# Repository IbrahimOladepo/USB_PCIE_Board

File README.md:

# USB PCIe Expansion Card

A PCI Express x1 to USB 3.0 expansion card, designed in KiCad. Plugs into a PCIe x1
slot and breaks it out to four USB 3.0 Type-A ports.

## Contents

- [Overview](#overview)
- [Board](#board)
- [Design approach](#design-approach)
- [First assembled board (v0.1)](#first-assembled-board-v01)
  - [The R25 bring-up bug and the through-hole fix](#the-r25-bring-up-bug-and-the-through-hole-fix)
  - [Running in a PC](#running-in-a-pc)
  - [Known issues](#known-issues-to-fix-in-the-next-revision)
- [Component sorting tray](#component-sorting-tray)
- [OS / driver setup](#os--driver-setup)
  - [Windows](#windows)
  - [Linux](#linux)
- [Repository layout](#repository-layout)
- [Status](#status)

## Overview

The design is built around **U1**, a Renesas `µPD720201` xHCI USB 3.0 host
controller, which bridges the PCIe link to four independent USB 3.0 ports.

| Function | Reference(s) | Part |
|---|---|---|
| PCIe x1 edge connector | J1 | `Bus_PCI_Express_x1` |
| USB host controller | U1 | Renesas `UPD720201K8-701-BAC-A` |
| Controller firmware/config flash | U2 | `MX25L4006EM1I-12G` (SPI NOR) |
| Controller clock | X1 | 24MHz crystal |
| USB 3.0 Type-A ports | J2–J5 | Molex `48406-0001` |
| Per-port VBUS power switches | U8–U11 | `AP2191SG-13` |
| Per-port ESD protection | U12–U15 | `SP3011-06UTG` |
| Power regulation | U3, U4, U5, U7 | Buck regulators + 3.3V LDO |

Power for the board and its 5V VBUS rails is derived from the PCIe slot's 12V/3.3V
supply through an on-board regulation chain.

## Board

- 4-layer, ~98.6 x 111.9mm
- ~175 components, ~126 nets

| Top | Bottom |
|---|---|
|  |  |

## Design approach

- **All tracks were routed by hand.** No autorouter and no AI-generated routing was
  used.
- **The layer stackup was worked out by me**, following recommendations from
  experts such as Rick Hartley.
- **Claude (Anthropic's AI assistant) was used for repository version control and as
  a second pair of eyes for checking nets for errors.** It did not route or place
  anything. Layout and design decisions are my own.

## First assembled board (v0.1)

| Top | Bottom |
|---|---|
|  |  |

### The R25 bring-up bug and the through-hole fix

The first populated board brought up all rails cleanly except the 1.05V core rail
(U5), which came up equal to its input voltage instead of regulating. Bring-up debug
(solder-bridge check, continuity check, a U5 swap that didn't help) eventually traced
it to the feedback divider: **R25 had been sourced as a 133Ω part instead of the
133kΩ the design called for**, a unit typo (Ω vs kΩ) that slipped through to the BOM
and the order. With R24 (100kΩ, correct) on top and a 133Ω part on the bottom, the
feedback node was pulled to nearly 0V, which made the regulator's control loop drive
close to 100% duty cycle: output tracking input, exactly as observed.

The through-hole resistors visible in the top-view photo (bottom right, near L3/D14)
are the quick fix: a **100kΩ + 33kΩ series pair (133kΩ total)** from parts already on
hand, soldered in place of the bad R25 so the divider is back at its design value
(1.05V output) without waiting on a new part order.

### Running in a PC

The board is plugged into the PC's PCIe slot through a **PCIe riser**, for two
reasons: it makes the board easy to probe with a multimeter while powered, and the
case has no room for the board's USB connector placement when seated directly in the
slot. The annotated photo marks the R25 fix and the riser. The original,
un-annotated photo is
[`2D/Photos/20260920_213102.jpg`](2D/Photos/20260920_213102.jpg).

A 1TB SSD connected to one of the board's USB ports, tested with CrystalDiskMark:

| Test | Read (MB/s) | Write (MB/s) |
|---|---|---|
| SEQ1M Q8T1 | 400.00 | 384.33 |
| SEQ1M Q1T1 | 376.39 | 365.24 |
| RND4K Q32T1 | 152.30 | 153.49 |
| RND4K Q1T1 | 22.54 | 40.38 |

### Known issues (to fix in the next revision)

- **1.05V indicator LED (D11) cannot light.** D11 is a blue `SMLMN2BCTT86C` with a
  forward voltage of about 2.9V, but it is wired across the 1.05V rail, so it can
  never turn on. Note that swapping to a lower-Vf colour will not fix this on its own:
  a red/yellow/green LED still needs roughly 1.8V or more. Options for v0.2: drive
  the LED from +3V3 through a resistor and switch it with a small transistor sensed
  from +1V05, or drop the LED and rely on the TP6/TP7 test points.
- **R25 value.** Re-check the schematic/BOM value and the ordered part for R25 so they
  match the intended 133kΩ before the next order.
- See [`Doc/PCB_Design_Review_Checklist.md`](Doc/PCB_Design_Review_Checklist.md) for the
  rest of the v0.1 review notes.

## Component sorting tray

A 150 x 150 x 10mm box-and-lid pair for sorting the BOM by hand before assembly, one
compartment per distinct part/value. Generated with the
[box-stl-generator](https://javisperez.github.io/box-stl-generator/) tool; STL files
are in `3D/Assembly/`. Pair it with `Doc/Component_Tray_Layout.pdf` for a printable,
to-scale cut-out label plus a lookup table mapping each compartment to its BOM entry.

| Box | Lid |
|---|---|
|  |  |

## OS / driver setup

### Windows

Windows Update alone was enough to bring the controller up correctly. In addition, the
[Renesas USB 3.0 Host Controller Driver](https://www.dell.com/support/home/en-fm/drivers/driversdetails?driverid=1ptn7)
(distributed via Dell's driver site) was installed. No manual firmware extraction step
was needed on Windows, unlike Linux.

### Linux

This board uses the Renesas `UPD720201K8-701-BAC-A` PCIe to USB 3.0 host controller. On
Linux, the `xhci-pci-renesas` driver requires a firmware blob to bring the controller
online. That firmware is not distributed through the standard `linux-firmware` package
due to Renesas licensing restrictions, so it has to be installed manually. The steps
below worked on Ubuntu (kernel 7.0.x).

**1. Confirm the board is enumerating on PCIe**

Before touching firmware, confirm the OS sees the chip at all:

```bash
lspci -d 1912:
```

If nothing shows up, this is a hardware bring-up issue (power sequencing, REFCLK/PERST#
timing, card edge connector, or PCIe slot lane availability), not a firmware issue.
Check `sudo dmesg | grep -iE "pci|xhci"` around boot time for enumeration messages
before proceeding.

Once the chip enumerates correctly, you'll see something like:

```
xhci-pci-renesas 0000:01:00.0: probe with driver xhci-pci-renesas failed with error -2
```

The `-2` (ENOENT) confirms the driver bound successfully but could not find the
firmware file.

**2. Get the firmware**

The `linux-firmware` package does not ship `renesas_usb_fw.mem` for this chip family.
Use the community-maintained mirror instead, which repackages the firmware extracted
from Renesas's official Windows update tool along with checksums:

```bash
cd /tmp
wget https://github.com/chunkeey/renesas-fw/raw/master/USB3-201-202-FW-20120615.zip
wget https://github.com/chunkeey/renesas-fw/raw/master/SHA256SUMS
sha256sum -c SHA256SUMS 2>/dev/null | grep -i ok
unzip USB3-201-202-FW-20120615.zip -d renesas-fw-extracted
```

This covers both the uPD720201 and uPD720202 with a single combined firmware image:
`K2013080.mem`.

**3. Install the firmware**

```bash
sudo cp /tmp/renesas-fw-extracted/USB3-201-202-FW-20120615/K2013080.mem /lib/firmware/renesas_usb_fw.mem
file /lib/firmware/renesas_usb_fw.mem   # should report "data", not ASCII/HTML
sudo update-initramfs -u
sudo reboot
```

**4. Verify**

```bash
sudo dmesg | grep -i renesas
lsusb
```

Expected output on success:

```
xhci-pci-renesas 0000:01:00.0: xHCI Host Controller
xhci-pci-renesas 0000:01:00.0: new USB bus registered, assigned bus number 3
xhci-pci-renesas 0000:01:00.0: new USB bus registered, assigned bus number 4
xhci-pci-renesas 0000:01:00.0: Host supports USB 3.0 SuperSpeed
usb 4-1: new SuperSpeed USB device number 2 using xhci-pci-renesas
```

A device plugged into the hub should now show up in `lsusb` as a SuperSpeed device on
the new bus.

**Notes**

- This firmware image is dated 2012. Renesas has released newer versions since; if you
  hit driver errors that this image does not resolve, pull an updated version directly
  from Renesas's site (free account required) rather than a community mirror.
- Because the firmware is not redistributable through `linux-firmware`, this manual
  install step will need to be repeated after a fresh OS install or if `/lib/firmware`
  gets wiped. Consider scripting steps 2 to 3 as a setup script in this repo for future
  bring-up.

## Repository layout

- `USB_PCIE_Board.kicad_pro` / `.kicad_pcb` / `.kicad_sch` — main project, board, and schematic
- `USB_PCIE_BOARD_POWER.kicad_sch` — power supply schematic sheet
- `Doc/` — documentation, including a PCB design review checklist and the component
  tray layout
- `2D/` — board edge outline drawings (`.dxf` / `.ai`), and `2D/Photos/` with photos of
  the assembled v0.1 board and its bring-up
- `3D/` — Blender renders and STEP/pcb3d exports of the board; `3D/Assembly/` has the
  sorting tray's STL files and renders
- `bom/` — interactive HTML BOM (`ibom.html`)
- `production/` — generated fabrication outputs (gerbers, BOM, position files)

## Status

Actively being worked through a design review pass (DRC cleanup, courtyard/footprint
fixes, silkscreen check) — see `Doc/PCB_Design_Review_Checklist.md` for the current
punch list.

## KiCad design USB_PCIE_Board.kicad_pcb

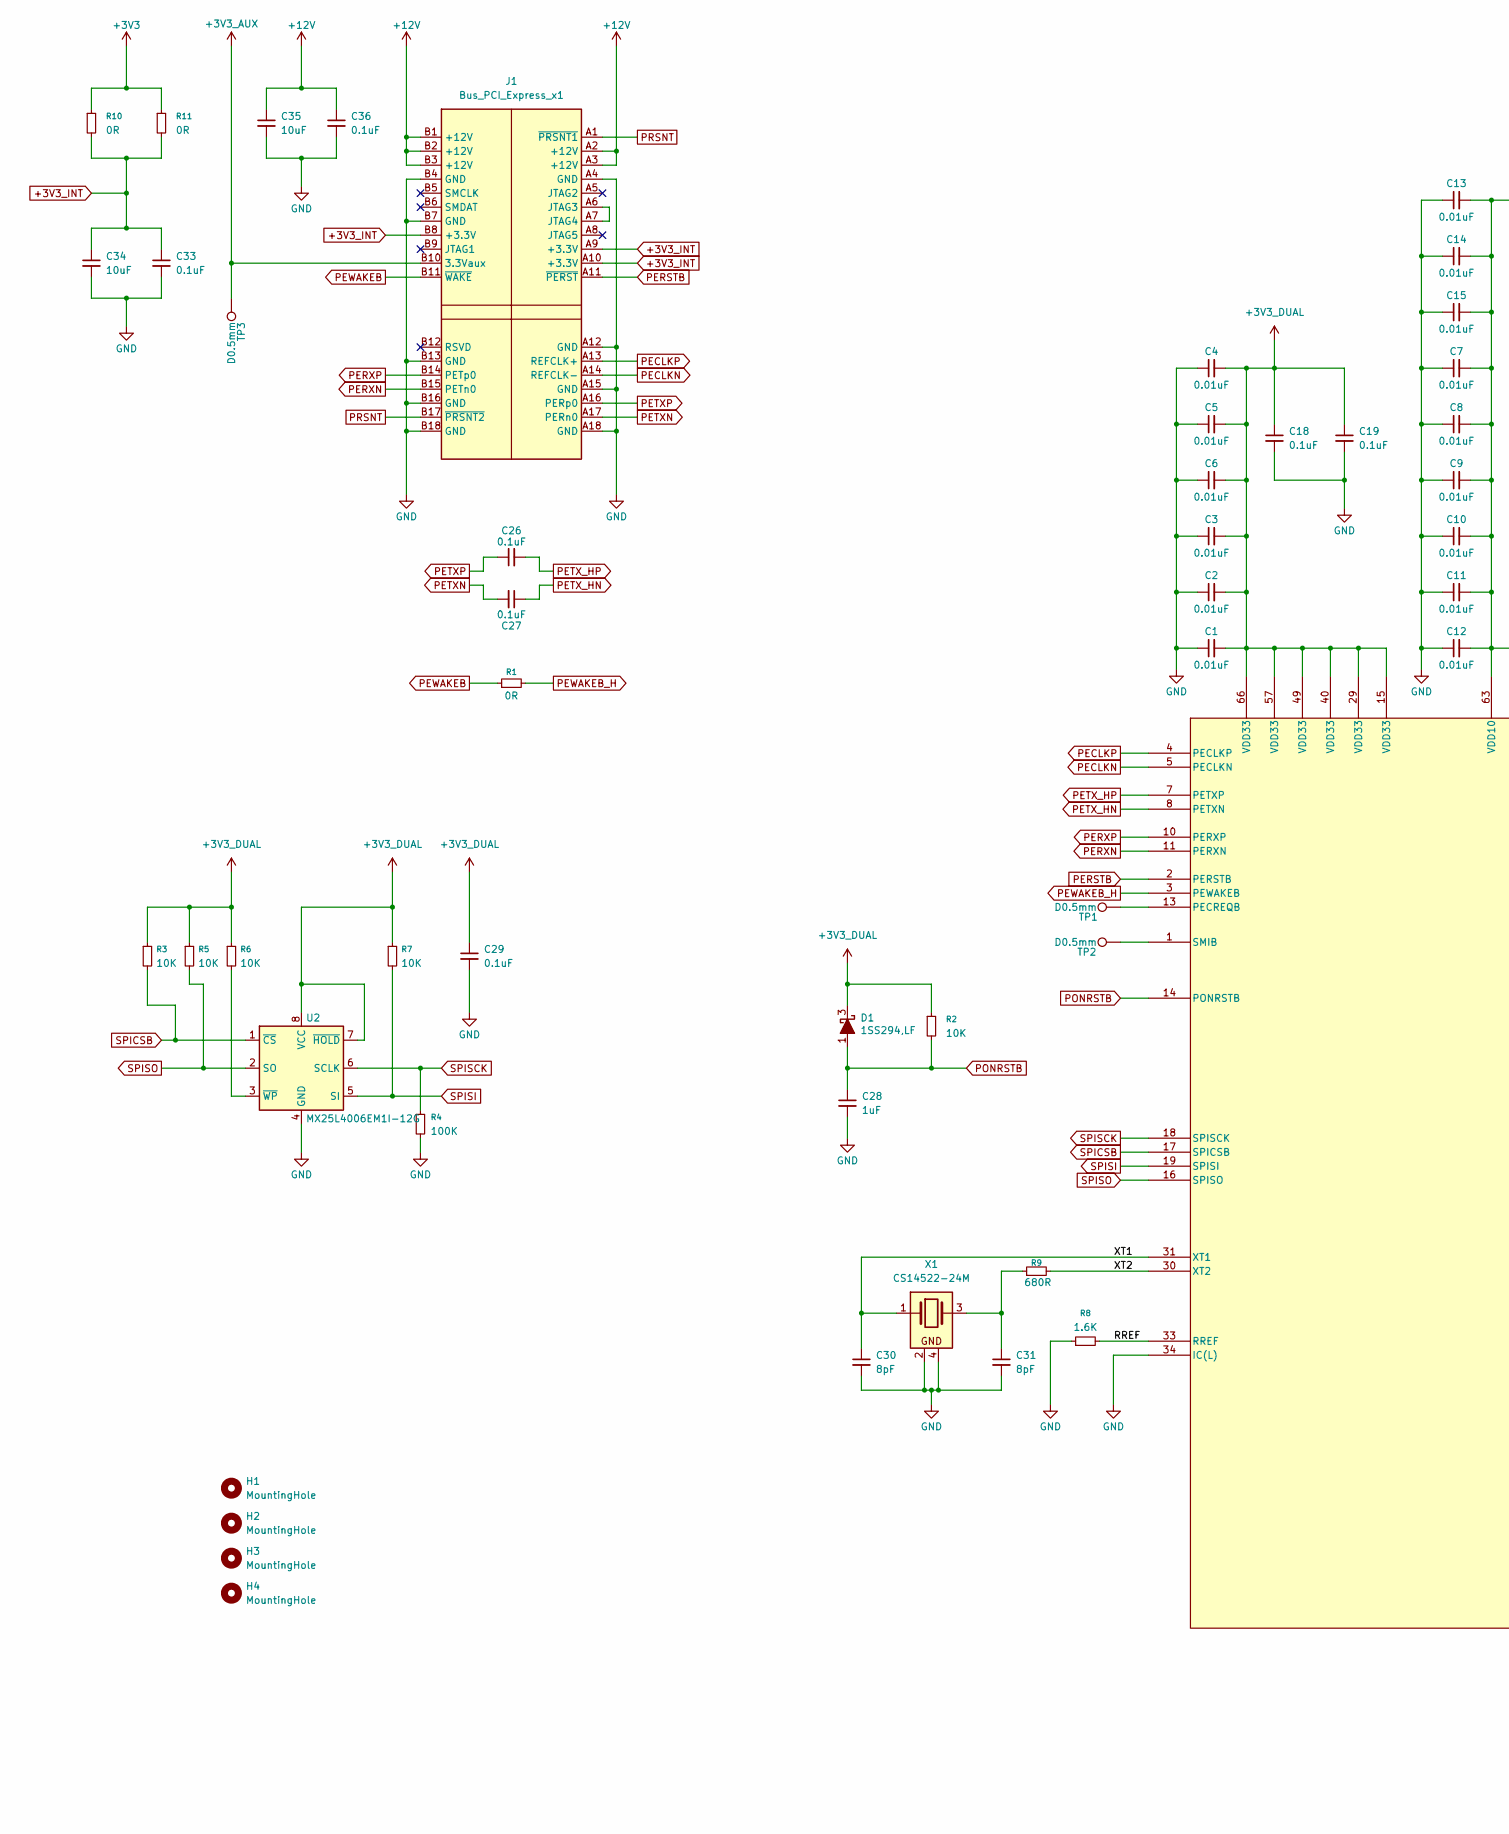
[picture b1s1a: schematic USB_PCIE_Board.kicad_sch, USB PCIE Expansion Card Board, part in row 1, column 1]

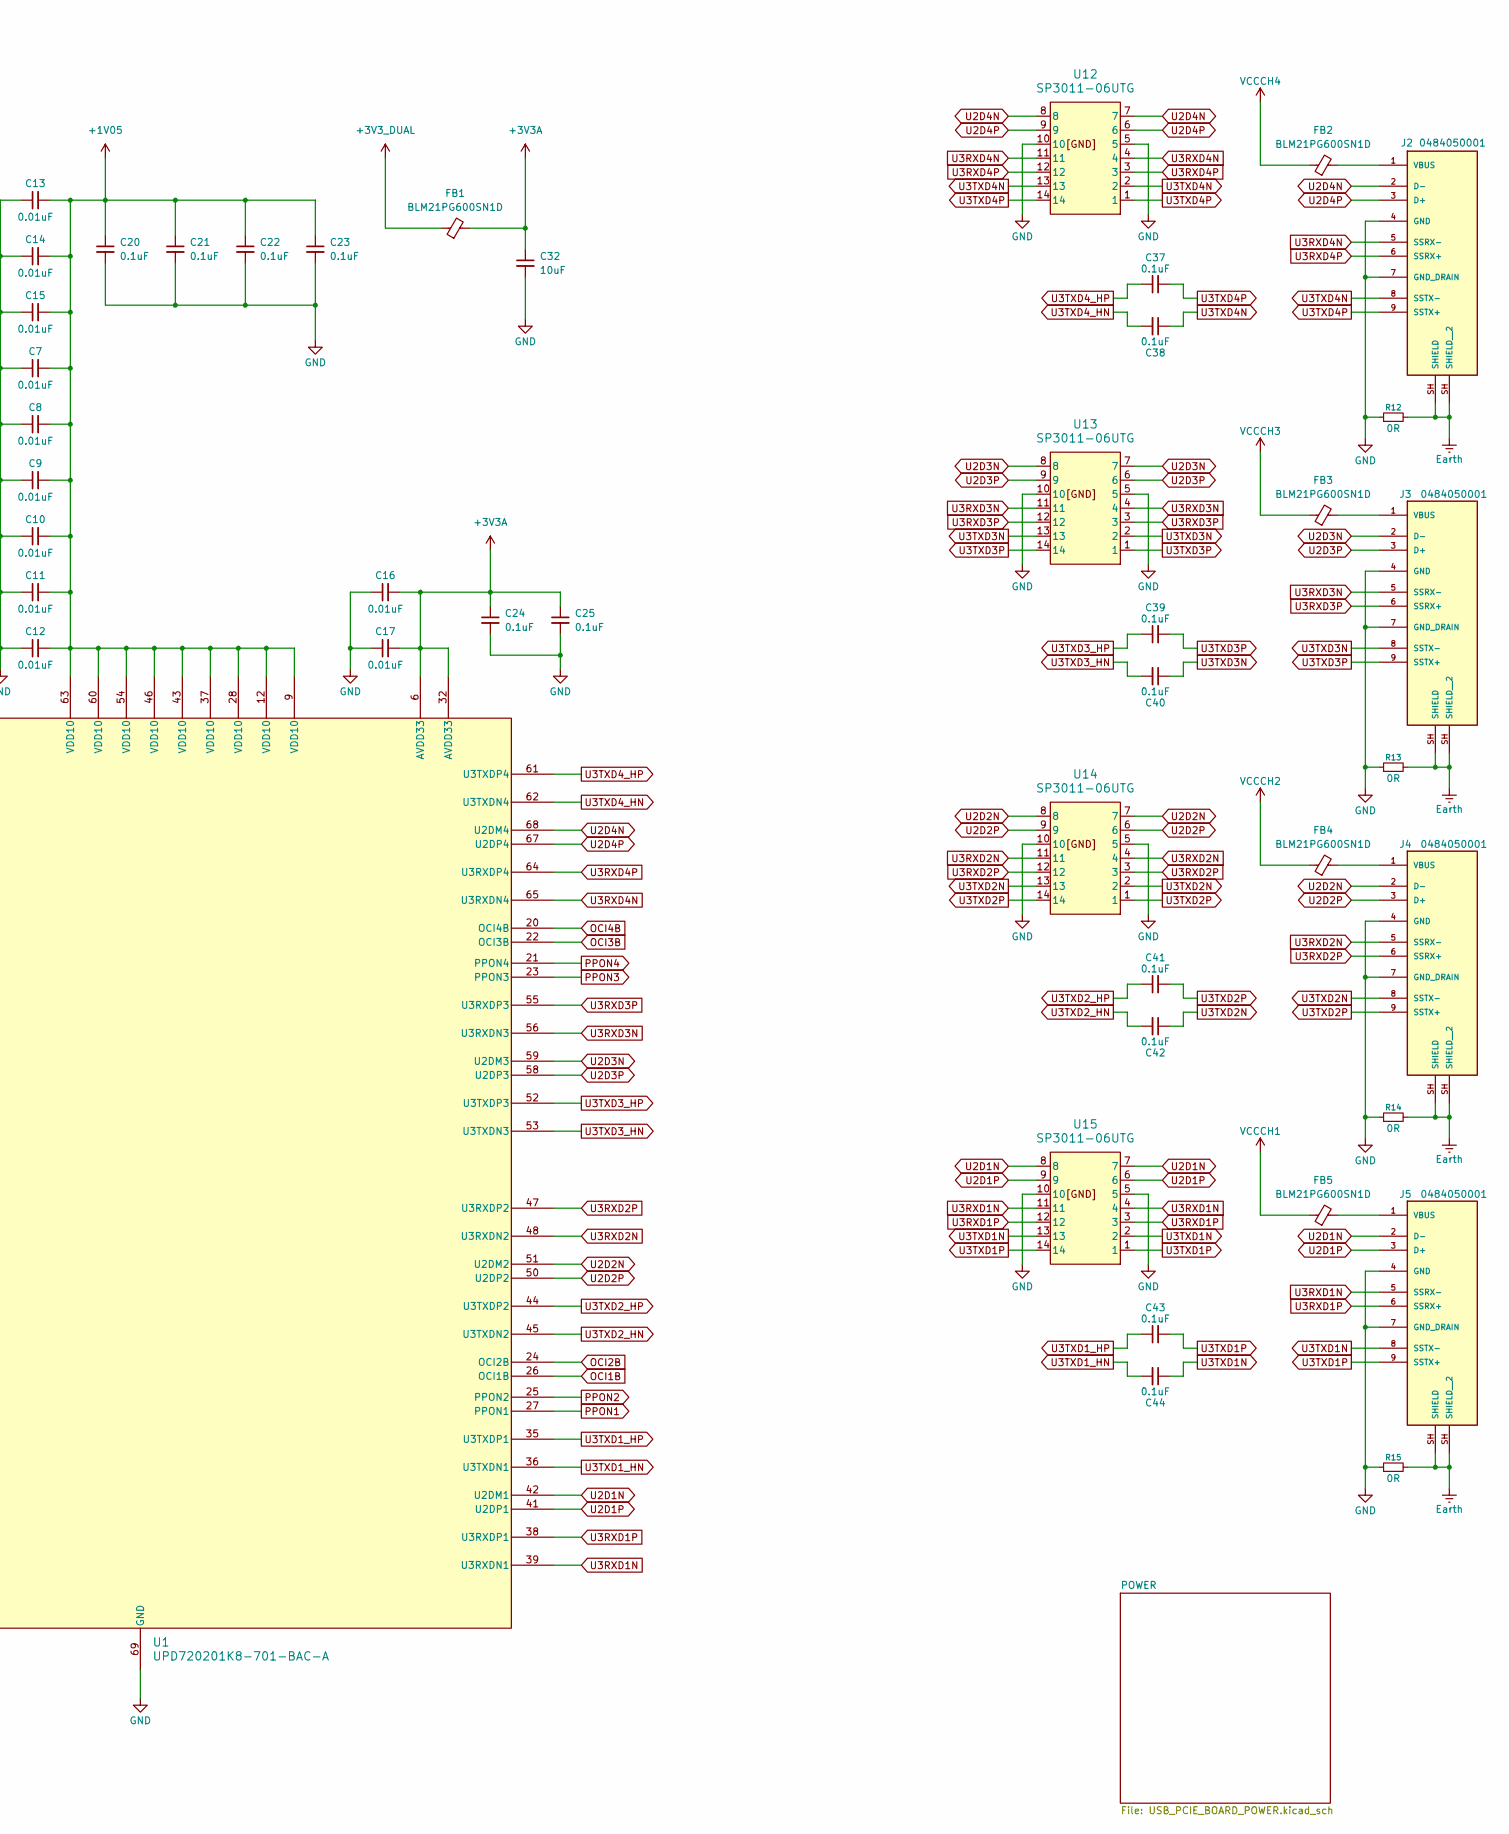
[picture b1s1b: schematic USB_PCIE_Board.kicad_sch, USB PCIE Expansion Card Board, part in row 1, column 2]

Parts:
C1, C2, C3, C4, C5, C6, C7, C8, C9, C10, C11, C12, C13, C14, C15, C16, C17: 0.01uF; C_0402_1005Metric_Pad0.74x0.62mm_HandSolder; Manufacturer Part # CC0402KRX7R9BB103; DigiKey Part # 311-1349-1-ND
C18, C19, C20, C21, C22, C23, C24, C25, C26, C27, C29, C37, C38, C39, C40, C41, C42, C43, C44: 0.1uF; C_0402_1005Metric_Pad0.74x0.62mm_HandSolder; Voltage Rating 16V; Manufacturer Part # CC0402KRX7R7BB104; DigiKey Part # C60474
C28: 1uF; C_0603_1608Metric_Pad1.08x0.95mm_HandSolder; Voltage Rating 25V; Manufacturer Part # CL10B105KA8NNNC; DigiKey Part # 1276-1184-1-ND
C30, C31: 8pF; C_0402_1005Metric_Pad0.74x0.62mm_HandSolder; Voltage Rating 50V; Manufacturer Part # GJM1555C1H8R0DB01D; DigiKey Part # 490-GJM1555C1H8R0DB01DCT-ND
C32, C34: 10uF; C_0805_2012Metric_Pad1.18x1.45mm_HandSolder; Voltage Rating 16V; Manufacturer Part # CC0805KKX7R7BB106; DigiKey Part # 311-3501-1-ND
C33, C36: 0.1uF; C_0603_1608Metric_Pad1.08x0.95mm_HandSolder; Voltage Rating 50V; Manufacturer Part # CC0603KRX7R9BB104; DigiKey Part # C14663
C35: 10uF; C_1206_3216Metric_Pad1.33x1.80mm_HandSolder; Voltage Rating 25V; Manufacturer Part # GRM319R61E106KA12D; DigiKey Part # 490-5525-1-ND
D1: 1SS294,LF; SC-59; Manufacturer Part # 1SS294,LF; DigiKey Part # 1SS294LFCT-ND
FB1, FB2, FB3, FB4, FB5: BLM21PG600SN1D; Ferrite_0805_2012Metric_BigPads; Manufacturer Part # BLM21PG600SN1D; DigiKey Part # 490-1053-1-ND
H1, H2, H3, H4: MountingHole; MountingHole_3.2mm_M3
J1: Bus_PCI_Express_x1; BUS_PCIexpress_x1
J2, J3, J4, J5: 0484050001; USB3_A_Molex_48406-0001_Horizontal_Stacked; Manufacturer Part # 0484050001; DigiKey Part # 0484050001-ND
R1, R12, R13, R14, R15: 0R; R_0603_1608Metric_Pad0.98x0.95mm_HandSolder; Manufacturer Part # RC0603JR-070RL; DigiKey Part # 311-0.0GRCT-ND
R2, R3, R5, R6, R7: 10K; R_0603_1608Metric_Pad0.98x0.95mm_HandSolder; Tolerance 5%; Manufacturer Part # RK73B1JTTD103J; DigiKey Part # 2019-RK73B1JTTD103JCT-ND
R4: 100K; R_0603_1608Metric_Pad0.98x0.95mm_HandSolder; Tolerance 1%; Manufacturer Part # RC0603FR-07100KL; DigiKey Part # 311-100KHRCT-ND
R8: 1.6K; R_0402_1005Metric_Pad0.72x0.64mm_HandSolder; Tolerance 1%; Manufacturer Part # ERJ-2RKF1601X; DigiKey Part # P1.60KLCT-ND
R9: 680R; R_0402_1005Metric_Pad0.72x0.64mm_HandSolder; Manufacturer Part # ERJ2RKF6800X; DigiKey Part # 10-ERJ-H2RF6800XCT-ND
R10, R11: 0R; R_1206_3216Metric_Pad1.30x1.75mm_HandSolder; Manufacturer Part # RK73Z2BTTD; DigiKey Part # 2019-RK73Z2BTTDCT-ND
TP1, TP2, TP3: D0.5mm; TestPoint_THTPad_1.0x1.0mm_Drill0.5mm
U1: UPD720201K8-701-BAC-A; QFN68_8X8_REN-M; Manufacturer Part # UPD720201K8-701-BAC-A; DigiKey Part # UPD720201K8-701-BAC-A-ND
U2: MX25L4006EM1I-12G; HSOP-8-1EP_3.9x4.9mm_P1.27mm_EP2.3x2.3mm_FLASH; Manufacturer Part # MX25L4006EM1I-12G; DigiKey Part # 1092-1114-ND
U12, U13, U14, U15: SP3011-06UTG; SON14_SP3011-06UTG_LTF-M; Manufacturer Part # SP3011-06UTG; DigiKey Part # F3579CT-ND
X1: CS14522-24M; Crystal_SMD_3225-4Pin_3.2x2.5mm_HandSoldering; Manufacturer Part # CS14522-24M; DigiKey Part # 644-CS14522-24MCT-ND

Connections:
+1V05: C7.2, C8.2, C9.2, C10.2, C11.2, C12.2, C13.2, C14.2, C15.2, C20.1, C21.1, C22.1, C23.1, U1.9 (VDD10), U1.12 (VDD10), U1.28 (VDD10), U1.37 (VDD10), U1.43 (VDD10), U1.46 (VDD10), U1.54 (VDD10), U1.60 (VDD10), U1.63 (VDD10); also elsewhere on the board
+3V3: R10.1, R11.1; also elsewhere on the board
+3V3A: C16.2, C17.2, C24.1, C25.1, C32.1, FB1.2, U1.6 (AVDD33), U1.32 (AVDD33)
+3V3_AUX: J1.B10 (3.3Vaux), TP3.1 (1_1)
+3V3_DUAL: C1.2, C2.2, C3.2, C4.2, C5.2, C6.2, C18.1, C19.1, C29.1, D1.3 (K), FB1.1, R2.1, R3.1, R5.1, R6.1, R7.1, U1.15 (VDD33), U1.29 (VDD33), U1.40 (VDD33), U1.49 (VDD33), U1.57 (VDD33), U1.66 (VDD33), U2.7 (~HOLD), U2.8 (VCC); also elsewhere on the board
+3V3_INT: C33.1, C34.1, J1.A9 (+3.3V), J1.A10 (+3.3V), J1.B8 (+3.3V), R10.2, R11.2
+12V: C35.1, C36.1, J1.A2 (+12V), J1.A3 (+12V), J1.B1 (+12V), J1.B2 (+12V), J1.B3 (+12V); also elsewhere on the board
/RREF: R8.2, U1.33 (RREF)
/XT1: C30.1, U1.31 (XT1), X1.1
/XT2: R9.2, U1.30 (XT2)
Earth: J2.SH (SHIELD), J3.SH (SHIELD), J4.SH (SHIELD), J5.SH (SHIELD), R12.2, R13.2, R14.2, R15.2
GND: C1.1, C2.1, C3.1, C4.1, C5.1, C6.1, C7.1, C8.1, C9.1, C10.1, C11.1, C12.1, C13.1, C14.1, C15.1, C16.1, C17.1, C18.2, C19.2, C20.2, C21.2, C22.2, C23.2, C24.2, C25.2, C28.2, C29.2, C30.2, C31.2, C32.2, C33.2, C34.2, C35.2, C36.2, J1.A4 (GND), J1.A12 (GND), J1.A15 (GND), J1.A18 (GND), J1.B4 (GND), J1.B7 (GND), J1.B13 (GND), J1.B16 (GND), J1.B18 (GND), J2.4 (GND), J2.7 (GND_DRAIN), J3.4 (GND), J3.7 (GND_DRAIN), J4.4 (GND), J4.7 (GND_DRAIN), J5.4 (GND), J5.7 (GND_DRAIN), R4.2, R8.1, R12.1, R13.1, R14.1, R15.1, U1.34 (IC(L)), U1.69 (GND), U2.4 (GND), U12.5, U12.10, U13.5, U13.10, U14.5, U14.10, U15.5, U15.10, X1.2, X1.4; also elsewhere on the board
unnamed: C31.1, R9.1, X1.3
unnamed: J1.A6 (JTAG3), J1.A7 (JTAG4)
unnamed: FB2.2, J2.1 (VBUS)
unnamed: FB3.2, J3.1 (VBUS)
unnamed: FB4.2, J4.1 (VBUS)
unnamed: FB5.2, J5.1 (VBUS)
unnamed: TP1.1 (1_1), U1.13 (PECREQB)
unnamed: TP2.1 (1_1), U1.1 (SMIB)
unnamed: R6.2, U2.3 (~WP)
OCI1B: U1.26 (OCI1B); also elsewhere on the board
OCI2B: U1.24 (OCI2B); also elsewhere on the board
OCI3B: U1.22 (OCI3B); also elsewhere on the board
OCI4B: U1.20 (OCI4B); also elsewhere on the board
PECLKN: J1.A14 (REFCLK-), U1.5 (PECLKN)
PECLKP: J1.A13 (REFCLK+), U1.4 (PECLKP)
PERSTB: J1.A11 (~PERST), U1.2 (PERSTB)
PERXN: J1.B15 (PETn0), U1.11 (PERXN)
PERXP: J1.B14 (PETp0), U1.10 (PERXP)
PETXN: C27.2, J1.A17 (PERn0)
PETXP: C26.1, J1.A16 (PERp0)
PETX_HN: C27.1, U1.8 (PETXN)
PETX_HP: C26.2, U1.7 (PETXP)
PEWAKEB: J1.B11 (~WAKE), R1.1
PEWAKEB_H: R1.2, U1.3 (PEWAKEB)
PONRSTB: C28.1, D1.1 (A), R2.2, U1.14 (PONRSTB)
PPON1: U1.27 (PPON1); also elsewhere on the board
PPON2: U1.25 (PPON2); also elsewhere on the board
PPON3: U1.23 (PPON3); also elsewhere on the board
PPON4: U1.21 (PPON4); also elsewhere on the board
PRSNT: J1.A1 (~PRSNT1), J1.B17 (~PRSNT2)
SPICSB: R3.2, U1.17 (SPICSB), U2.1 (~CS)
SPISCK: R4.1, U1.18 (SPISCK), U2.6 (SCLK)
SPISI: R7.2, U1.19 (SPISI), U2.5 (SI)
SPISO: R5.2, U1.16 (SPISO), U2.2 (SO)
U2D1N: J5.2 (D-), U1.42 (U2DM1), U15.7, U15.8
U2D1P: J5.3 (D+), U1.41 (U2DP1), U15.6, U15.9
U2D2N: J4.2 (D-), U1.51 (U2DM2), U14.7, U14.8
U2D2P: J4.3 (D+), U1.50 (U2DP2), U14.6, U14.9
U2D3N: J3.2 (D-), U1.59 (U2DM3), U13.7, U13.8
U2D3P: J3.3 (D+), U1.58 (U2DP3), U13.6, U13.9
U2D4N: J2.2 (D-), U1.68 (U2DM4), U12.7, U12.8
U2D4P: J2.3 (D+), U1.67 (U2DP4), U12.6, U12.9
U3RXD1N: J5.5 (SSRX-), U1.39 (U3RXDN1), U15.4, U15.11
U3RXD1P: J5.6 (SSRX+), U1.38 (U3RXDP1), U15.3, U15.12
U3RXD2N: J4.5 (SSRX-), U1.48 (U3RXDN2), U14.4, U14.11
U3RXD2P: J4.6 (SSRX+), U1.47 (U3RXDP2), U14.3, U14.12
U3RXD3N: J3.5 (SSRX-), U1.56 (U3RXDN3), U13.4, U13.11
U3RXD3P: J3.6 (SSRX+), U1.55 (U3RXDP3), U13.3, U13.12
U3RXD4N: J2.5 (SSRX-), U1.65 (U3RXDN4), U12.4, U12.11
U3RXD4P: J2.6 (SSRX+), U1.64 (U3RXDP4), U12.3, U12.12
U3TXD1N: C44.1, J5.8 (SSTX-), U15.2, U15.13
U3TXD1P: C43.2, J5.9 (SSTX+), U15.1, U15.14
U3TXD1_HN: C44.2, U1.36 (U3TXDN1)
U3TXD1_HP: C43.1, U1.35 (U3TXDP1)
U3TXD2N: C42.1, J4.8 (SSTX-), U14.2, U14.13
U3TXD2P: C41.2, J4.9 (SSTX+), U14.1, U14.14
U3TXD2_HN: C42.2, U1.45 (U3TXDN2)
U3TXD2_HP: C41.1, U1.44 (U3TXDP2)
U3TXD3N: C40.1, J3.8 (SSTX-), U13.2, U13.13
U3TXD3P: C39.2, J3.9 (SSTX+), U13.1, U13.14
U3TXD3_HN: C40.2, U1.53 (U3TXDN3)
U3TXD3_HP: C39.1, U1.52 (U3TXDP3)
U3TXD4N: C38.1, J2.8 (SSTX-), U12.2, U12.13
U3TXD4P: C37.2, J2.9 (SSTX+), U12.1, U12.14
U3TXD4_HN: C38.2, U1.62 (U3TXDN4)
U3TXD4_HP: C37.1, U1.61 (U3TXDP4)
VCCCH1: FB5.1; also elsewhere on the board
VCCCH2: FB4.1; also elsewhere on the board
VCCCH3: FB3.1; also elsewhere on the board
VCCCH4: FB2.1; also elsewhere on the board

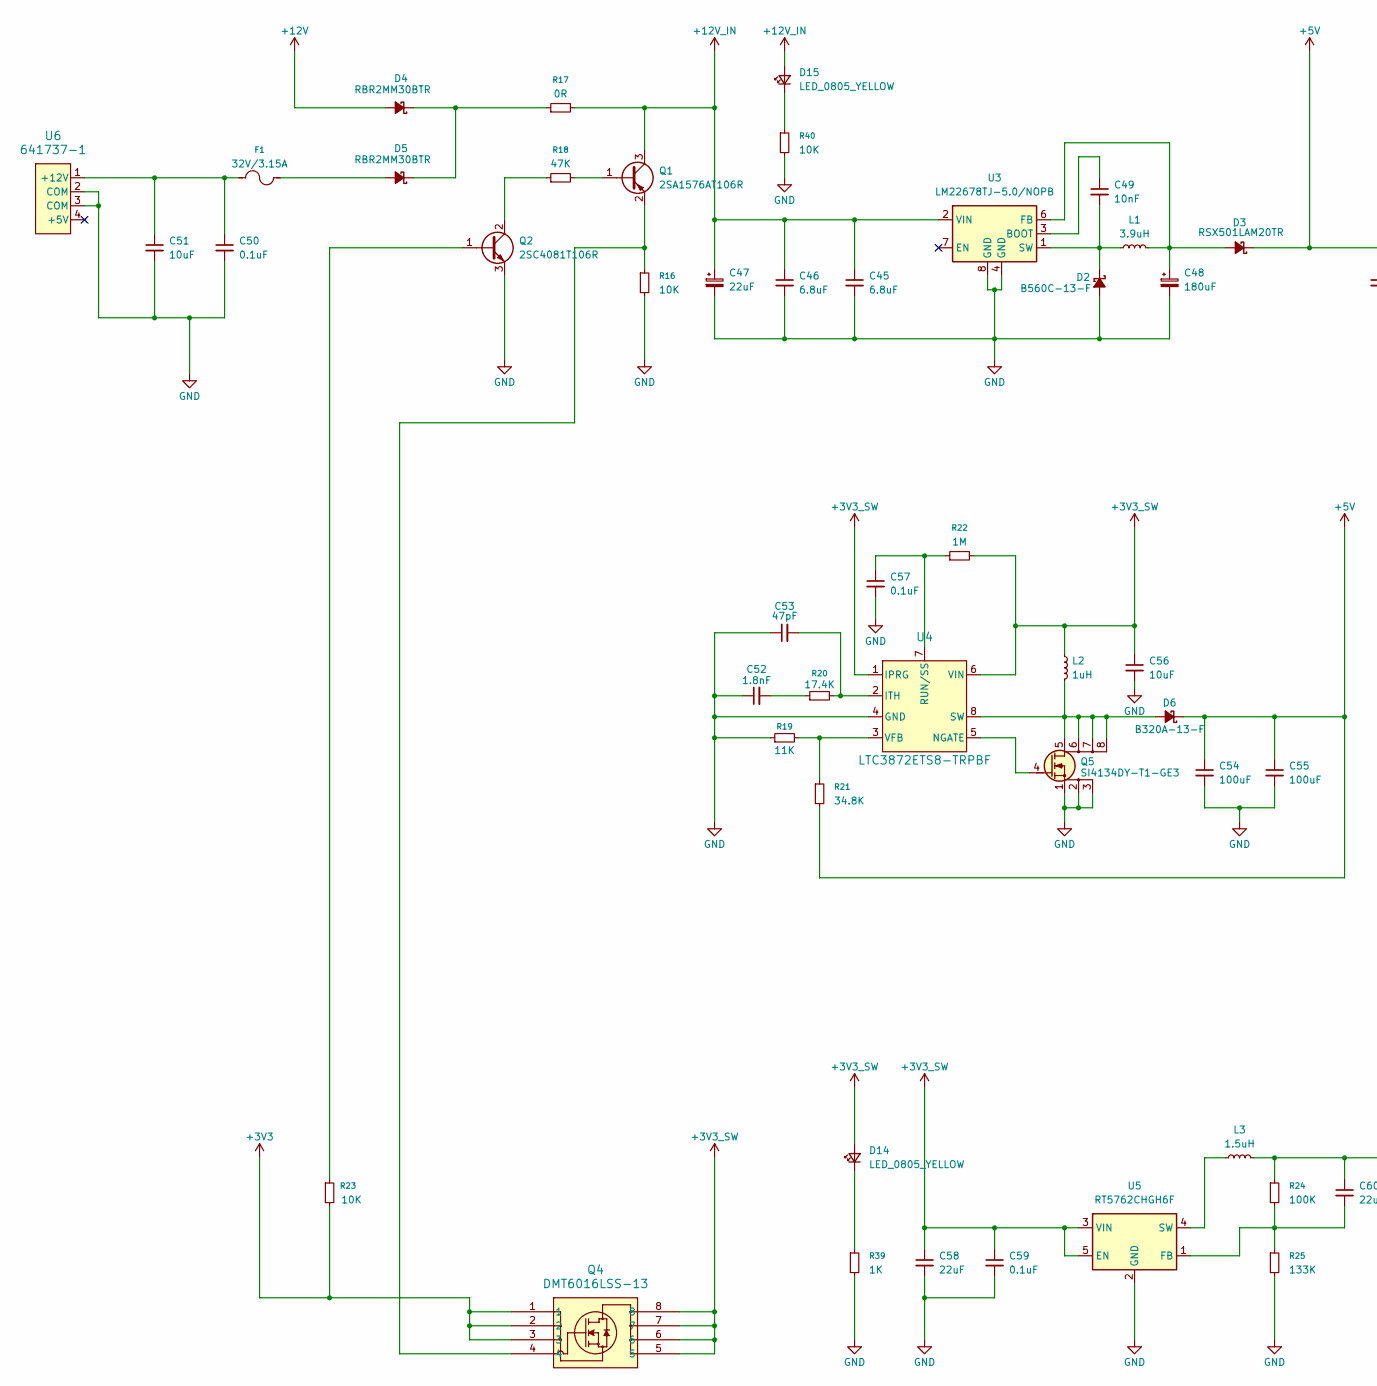
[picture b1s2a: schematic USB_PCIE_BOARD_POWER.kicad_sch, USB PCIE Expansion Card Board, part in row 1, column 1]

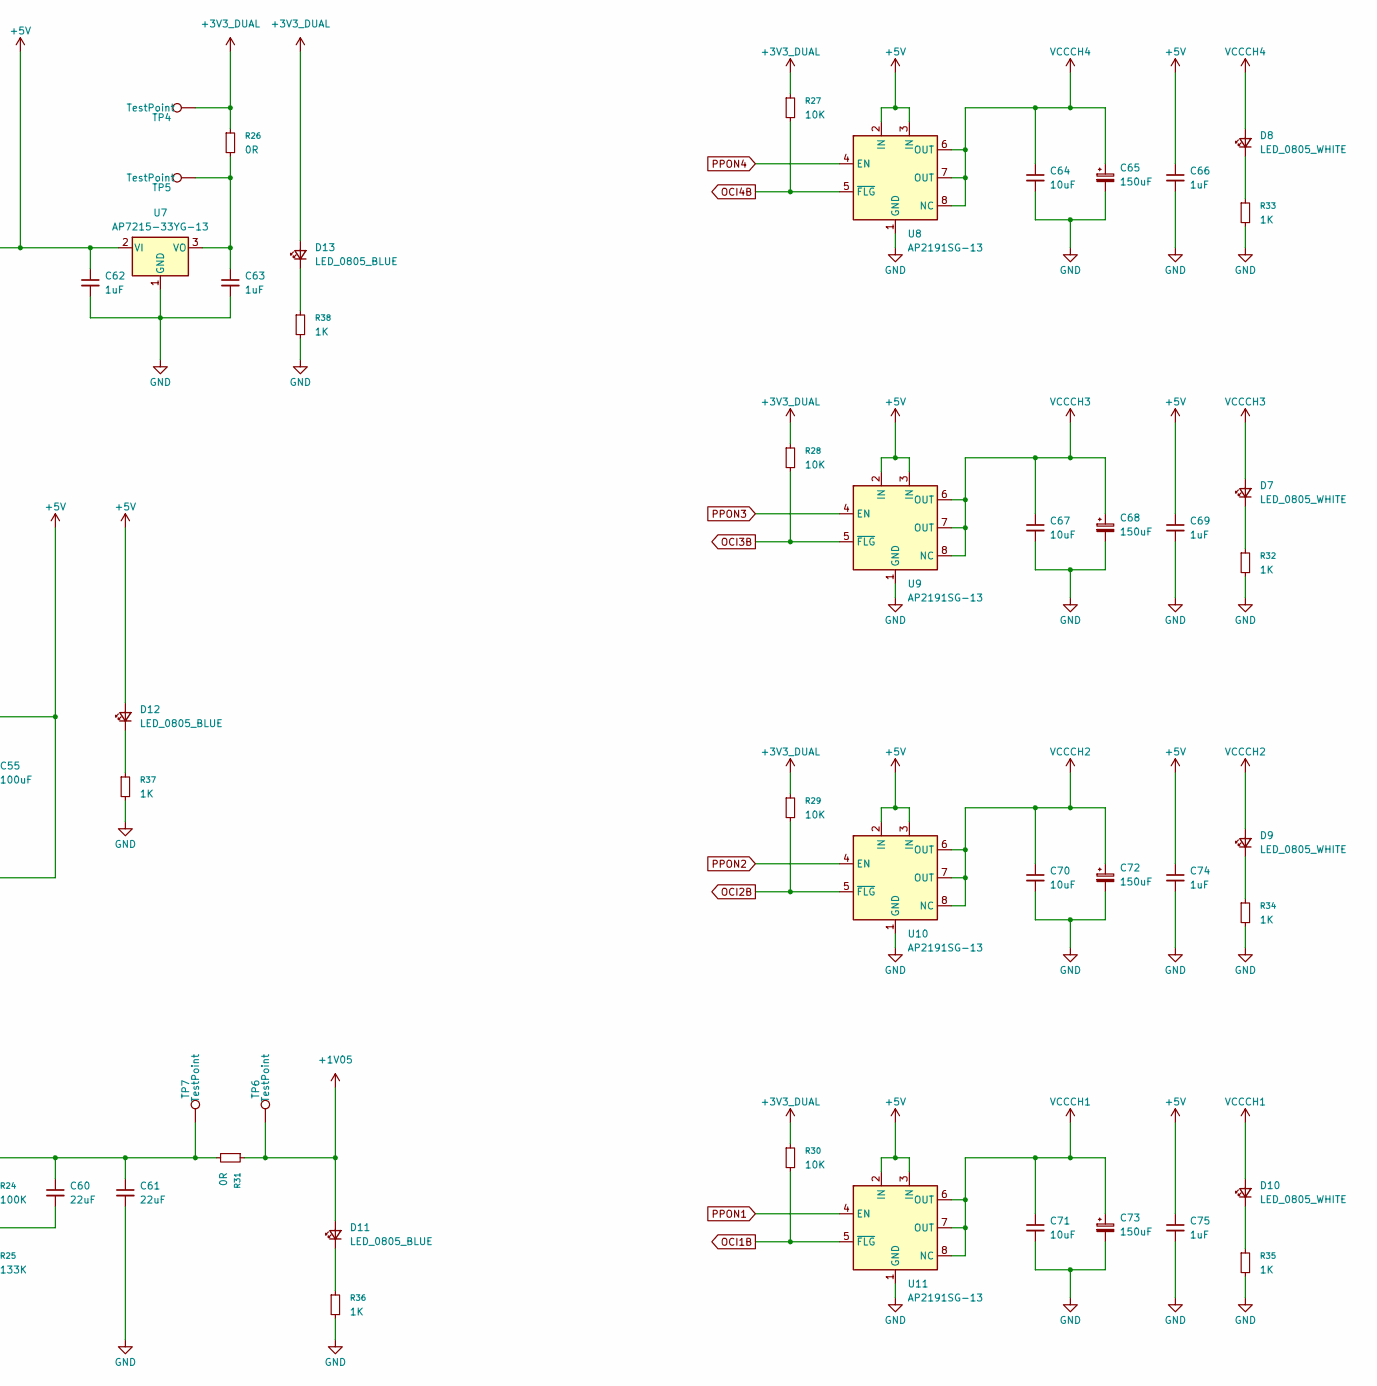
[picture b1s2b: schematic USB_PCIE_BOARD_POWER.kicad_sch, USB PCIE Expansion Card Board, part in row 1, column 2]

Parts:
C45, C46: 6.8uF; C_1206_3216Metric_Pad1.33x1.80mm_HandSolder; Voltage Rating 35V; Manufacturer Part # C3216X7R1V685K160AC; DigiKey Part # 445-14808-1-ND
C47: 22uF; CP_Elec_6.3x5.9; Voltage Rating 50V; Manufacturer Part # EEE-FK1H220P; DigiKey Part # PCE3811CT-ND
C48: 180uF; CP_Elec_8x10.5; Voltage Rating 50V; Manufacturer Part # EEE-FN1H181UP; DigiKey Part # 10-EEE-FN1H181UPCT-ND
C49: 10nF; C_1206_3216Metric_Pad1.33x1.80mm_HandSolder; Voltage Rating 50V; Manufacturer Part # CC1206KRX7R9BB103; DigiKey Part # 311-1174-1-ND
C50, C57, C59: 0.1uF; C_0603_1608Metric_Pad1.08x0.95mm_HandSolder; Voltage Rating 50V; Manufacturer Part # CC0603KRX7R9BB104; DigiKey Part # C14663
C51, C56: 10uF; C_1206_3216Metric_Pad1.33x1.80mm_HandSolder; Voltage Rating 25V; Manufacturer Part # GRM319R61E106KA12D; DigiKey Part # 490-5525-1-ND
C52: 1.8nF; C_0402_1005Metric_Pad0.74x0.62mm_HandSolder; Voltage Rating 50V; Manufacturer Part # CC0402KRX7R9BB182; DigiKey Part # 311-1721-1-ND
C53: 47pF; C_0402_1005Metric_Pad0.74x0.62mm_HandSolder; Voltage Rating 50V; Manufacturer Part # CC0402JRNPO9BN470; DigiKey Part # 311-1021-1-ND
C54, C55: 100uF; C_1210_3225Metric_Pad1.33x2.70mm_HandSolder; Voltage Rating 10V; Manufacturer Part # CL32A107MPVNNNE; DigiKey Part # 1276-3364-1-ND
C58, C60, C61: 22uF; C_0603_1608Metric_Pad1.08x0.95mm_HandSolder; Voltage Rating 6.3V; Manufacturer Part # GRM188R60J226MEA0D; DigiKey Part # 490-7611-1-ND
C62, C63, C66, C69, C74, C75: 1uF; C_0603_1608Metric_Pad1.08x0.95mm_HandSolder; Voltage Rating 25V; Manufacturer Part # CL10B105KA8NNNC; DigiKey Part # 1276-1184-1-ND
C64, C67, C70, C71: 10uF; C_0805_2012Metric_Pad1.18x1.45mm_HandSolder; Voltage Rating 16V; Manufacturer Part # CC0805KKX7R7BB106; DigiKey Part # 311-3501-1-ND
C65, C68, C72, C73: 150uF; CP_Elec_8x6.9; Voltage Rating 16V; Manufacturer Part # 16SVPC150M; DigiKey Part # 493-3776-1-ND
D2: B560C-13-F; D_SMC_Handsoldering; Manufacturer Part # B560C-13-F; DigiKey Part # B560C-FDICT-ND
D3: RSX501LAM20TR; D_SOD-128; Manufacturer Part # RSX501LAM20TR; DigiKey Part # RSX501LAM20CT-ND
D4, D5: RBR2MM30BTR; D_SOD-123F; Manufacturer Part # RBR2MM30BTR; DigiKey Part # RBR2MM30BCT-ND
D6: B320A-13-F; D_SMA; Voltage Rating 20V; Current Rating 3A; Manufacturer Part # B320A-13-F; DigiKey Part # B320A-FDICT-ND
D7, D8, D9, D10: LED_0805_WHITE; LED_0805_2012Metric_Pad1.15x1.40mm_HandSolder; Voltage Rating 2.9V; Manufacturer Part # SMLMN2WB1CW1; DigiKey Part # 846-SMLMN2WB1CW1CT-ND
D11, D12, D13: LED_0805_BLUE; LED_0805_2012Metric_Pad1.15x1.40mm_HandSolder; Voltage Rating 2.9V; Manufacturer Part # SMLMN2BCTT86C; DigiKey Part # 846-1207-1-ND
D14, D15: LED_0805_YELLOW; LED_0805_2012Metric_Pad1.15x1.40mm_HandSolder; Voltage Rating 1.85V; Manufacturer Part # APTD2012LSYCK; DigiKey Part # 754-2045-1-ND
F1: 32V/3.15A; Fuse_0603_1608Metric_Pad1.05x0.95mm_HandSolder; Voltage Rating 32V; Current Rating 3.15A; Manufacturer Part # SF-0603S315-2; DigiKey Part # SF-0603S315-2CT-ND
L1: 3.9uH; IND_BOURNS_SRU8043; Current Rating 4.8A; Manufacturer Part # SRU8043-3R9Y; DigiKey Part # SRU8043-3R9YCT-ND
L2: 1uH; IND_SPM6530T-1R0M120; Current Rating 13A; Manufacturer Part # SPM6530T-1R0M120; DigiKey Part # 445-3880-1-ND
L3: 1.5uH; L_1008_2520Metric_Pad1.43x2.20mm_HandSolder; Current Rating 2.7A; Manufacturer Part # DFE252012F-1R5M=P2; DigiKey Part # 490-13054-1-ND
Q1: 2SA1576AT106R; SOT-323_SC-70; Manufacturer Part # 2SA1576AT106R; DigiKey Part # 2SA1576AT106RCT-ND
Q2: 2SC4081T106R; SOT-323_SC-70; Manufacturer Part # 2SC4081T106R; DigiKey Part # 2SC4081T106RCT-ND
Q4: DMT6016LSS-13; SO-8; Current Rating 9.2A; Manufacturer Part # DMT6016LSS-13; DigiKey Part # DMT6016LSS-13DICT-ND
Q5: SI4134DY-T1-GE3; SO-8_3.9x4.9mm_P1.27mm; Voltage Rating 30V; Current Rating 14A; Manufacturer Part # SI4134DY-T1-GE3; DigiKey Part # SI4134DY-T1-GE3CT-ND
R16, R23, R27, R28, R29, R30, R40: 10K; R_0603_1608Metric_Pad0.98x0.95mm_HandSolder; Tolerance 5%; Manufacturer Part # RK73B1JTTD103J; DigiKey Part # 2019-RK73B1JTTD103JCT-ND
R17, R26, R31: 0R; R_1206_3216Metric_Pad1.30x1.75mm_HandSolder; Manufacturer Part # RK73Z2BTTD; DigiKey Part # 2019-RK73Z2BTTDCT-ND
R18: 47K; R_0603_1608Metric_Pad0.98x0.95mm_HandSolder; Tolerance 5%; Manufacturer Part # RC0603JR-0747KL; DigiKey Part # 311-47KGRCT-ND
R19: 11K; R_0402_1005Metric_Pad0.72x0.64mm_HandSolder; Voltage Rating 50V; Manufacturer Part # AF0402FR-0711KL; DigiKey Part # 13-AF0402FR-0711KLCT-ND
R20: 17.4K; R_0402_1005Metric_Pad0.72x0.64mm_HandSolder; Voltage Rating 50V; Manufacturer Part # CRCW040217K4FKED; DigiKey Part # 541-17.4KLCT-ND
R21: 34.8K; R_0402_1005Metric_Pad0.72x0.64mm_HandSolder; Voltage Rating 50V; Manufacturer Part # CRCW040234K8FKED; DigiKey Part # 541-34.8KLCT-ND
R22: 1M; R_0603_1608Metric_Pad0.98x0.95mm_HandSolder; Tolerance 1%; Manufacturer Part # CRCW06031M00FKEA; DigiKey Part # 541-1.00MHCT-ND
R24: 100K; R_0603_1608Metric_Pad0.98x0.95mm_HandSolder; Tolerance 1%; Manufacturer Part # RC0603FR-07100KL; DigiKey Part # 311-100KHRCT-ND
R25: 133K; R_0603_1608Metric_Pad0.98x0.95mm_HandSolder; Tolerance 1%; Manufacturer Part # CRCW0603133RFKEA; DigiKey Part # 541-133HCT-ND
R32, R33, R34, R35, R36, R37, R38, R39: 1K; R_0603_1608Metric_Pad0.98x0.95mm_HandSolder; Tolerance 1%; Manufacturer Part # RC0603FR-071KL; DigiKey Part # 311-1.00KHRCT-ND
TP4, TP5, TP6, TP7: TestPoint; TestPoint_THTPad_1.0x1.0mm_Drill0.5mm
U3: LM22678TJ-5.0/NOPB; TO-263-7_TabPin8; Voltage Rating 42V; Current Rating 5A; Manufacturer Part # LM22678TJ-5.0/NOPB; DigiKey Part # 296-49671-1-ND
U4: LTC3872ETS8-TRPBF; TSOT-23-8; Manufacturer Part # LTC3872ETS8#TRPBF; DigiKey Part # LTC3872ETS8#TRPBFCT-ND
U5: RT5762CHGH6F; SOT-563; Voltage Rating 6V; Current Rating 2A; Manufacturer Part # RT5762CHGH6F; DigiKey Part # 1028-RT5762CHGH6FCT-ND
U6: 641737-1; 641737-1_TYC; Manufacturer Part # 641737-1; DigiKey Part # A25430-ND
U7: AP7215-33YG-13; SOT-89-3; Current Rating 600mA; Manufacturer Part # AP7215-33YG-13; DigiKey Part # AP7215-33YG-13DICT-ND
U8, U9, U10, U11: AP2191SG-13; HSOP-8-1EP_3.9x4.9mm_P1.27mm_EP2.3x2.3mm; Manufacturer Part # AP2191SG-13; DigiKey Part # AP2191SGDICT-ND

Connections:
+1V05: D11.2 (A), R31.1, TP6.1 (1_1); also elsewhere on the board
+3V3: Q4.1, Q4.2, Q4.3, R23.2; also elsewhere on the board
+3V3_DUAL: D13.2 (A), R26.1, R27.1, R28.1, R29.1, R30.1, TP4.1 (1_1); also elsewhere on the board
+3V3_SW: C56.1, C58.1, C59.1, D14.2 (A), L2.1, Q4.5, Q4.6, Q4.7, Q4.8, R22.2, U4.1 (IPRG), U4.6 (VIN), U5.3 (VIN), U5.5 (EN)
+5V: C54.1, C55.1, C62.1, C66.1, C69.1, C74.1, C75.1, D3.1 (K), D6.1 (K), D12.2 (A), R21.2, U7.2 (VI), U8.2 (IN), U8.3 (IN), U9.2 (IN), U9.3 (IN), U10.2 (IN), U10.3 (IN), U11.2 (IN), U11.3 (IN)
+12V: D4.2 (A); also elsewhere on the board
+12V_IN: C45.1, C46.1, C47.1, D15.2 (A), Q1.3 (C), R17.2, U3.2 (VIN)
GND: C45.2, C46.2, C47.2, C48.2, C50.2, C51.2, C52.1, C53.1, C54.2, C55.2, C56.2, C57.2, C58.2, C59.2, C61.2, C62.2, C63.2, C64.2, C65.2, C66.2, C67.2, C68.2, C69.2, C70.2, C71.2, C72.2, C73.2, C74.2, C75.2, D2.2 (A), Q2.3 (E), Q5.1 (S), Q5.2 (S), Q5.3 (S), R16.2, R19.1, R25.2, R32.2, R33.2, R34.2, R35.2, R36.2, R37.2, R38.2, R39.2, R40.2, U3.4 (GND), U3.8 (GND), U4.4 (GND), U5.2 (GND), U6.2 (COM), U6.3 (COM), U7.1 (GND), U8.1 (GND), U9.1 (GND), U10.1 (GND), U11.1 (GND); also elsewhere on the board
unnamed: C52.2, R20.1
unnamed: C60.1, C61.1, L3.2, R24.1, R31.2, TP7.1 (1_1)
unnamed: C49.2, D2.1 (K), L1.1, U3.1 (SW)
unnamed: C48.1, D3.2 (A), L1.2, U3.6 (FB)
unnamed: D4.1 (K), D5.1 (K), R17.1
unnamed: D5.2 (A), F1.2
unnamed: D6.2 (A), L2.2, Q5.5 (D), Q5.6 (D), Q5.7 (D), Q5.8 (D), U4.8 (SW)
unnamed: D7.1 (K), R32.1
unnamed: D8.1 (K), R33.1
unnamed: D9.1 (K), R34.1
unnamed: D10.1 (K), R35.1
unnamed: D11.1 (K), R36.1
unnamed: D12.1 (K), R37.1
unnamed: D13.1 (K), R38.1
unnamed: D14.1 (K), R39.1
unnamed: D15.1 (K), R40.1
unnamed: Q1.1 (B), R18.2
unnamed: Q1.2 (E), Q4.4, R16.1
unnamed: Q2.1 (B), R23.1
unnamed: Q2.2 (C), R18.1
unnamed: Q5.4 (G), U4.5 (NGATE)
unnamed: C49.1, U3.3 (BOOT)
unnamed: C53.2, R20.2, U4.2 (ITH)
unnamed: C57.1, R22.1, U4.7 (RUN/SS)
unnamed: R19.2, R21.1, U4.3 (VFB)
unnamed: C60.2, R24.2, R25.1, U5.1 (FB)
unnamed: L3.1, U5.4 (SW)
unnamed: C50.1, C51.1, F1.1, U6.1 (+12V)
unnamed: C63.1, R26.2, TP5.1 (1_1), U7.3 (VO)
OCI1B: R30.2, U11.5 (~FLG); also elsewhere on the board
OCI2B: R29.2, U10.5 (~FLG); also elsewhere on the board
OCI3B: R28.2, U9.5 (~FLG); also elsewhere on the board
OCI4B: R27.2, U8.5 (~FLG); also elsewhere on the board
PPON1: U11.4 (EN); also elsewhere on the board
PPON2: U10.4 (EN); also elsewhere on the board
PPON3: U9.4 (EN); also elsewhere on the board
PPON4: U8.4 (EN); also elsewhere on the board
VCCCH1: C71.1, C73.1, D10.2 (A), U11.6 (OUT), U11.7 (OUT), U11.8 (NC); also elsewhere on the board
VCCCH2: C70.1, C72.1, D9.2 (A), U10.6 (OUT), U10.7 (OUT), U10.8 (NC); also elsewhere on the board
VCCCH3: C67.1, C68.1, D7.2 (A), U9.6 (OUT), U9.7 (OUT), U9.8 (NC); also elsewhere on the board
VCCCH4: C64.1, C65.1, D8.2 (A), U8.6 (OUT), U8.7 (OUT), U8.8 (NC); also elsewhere on the board
